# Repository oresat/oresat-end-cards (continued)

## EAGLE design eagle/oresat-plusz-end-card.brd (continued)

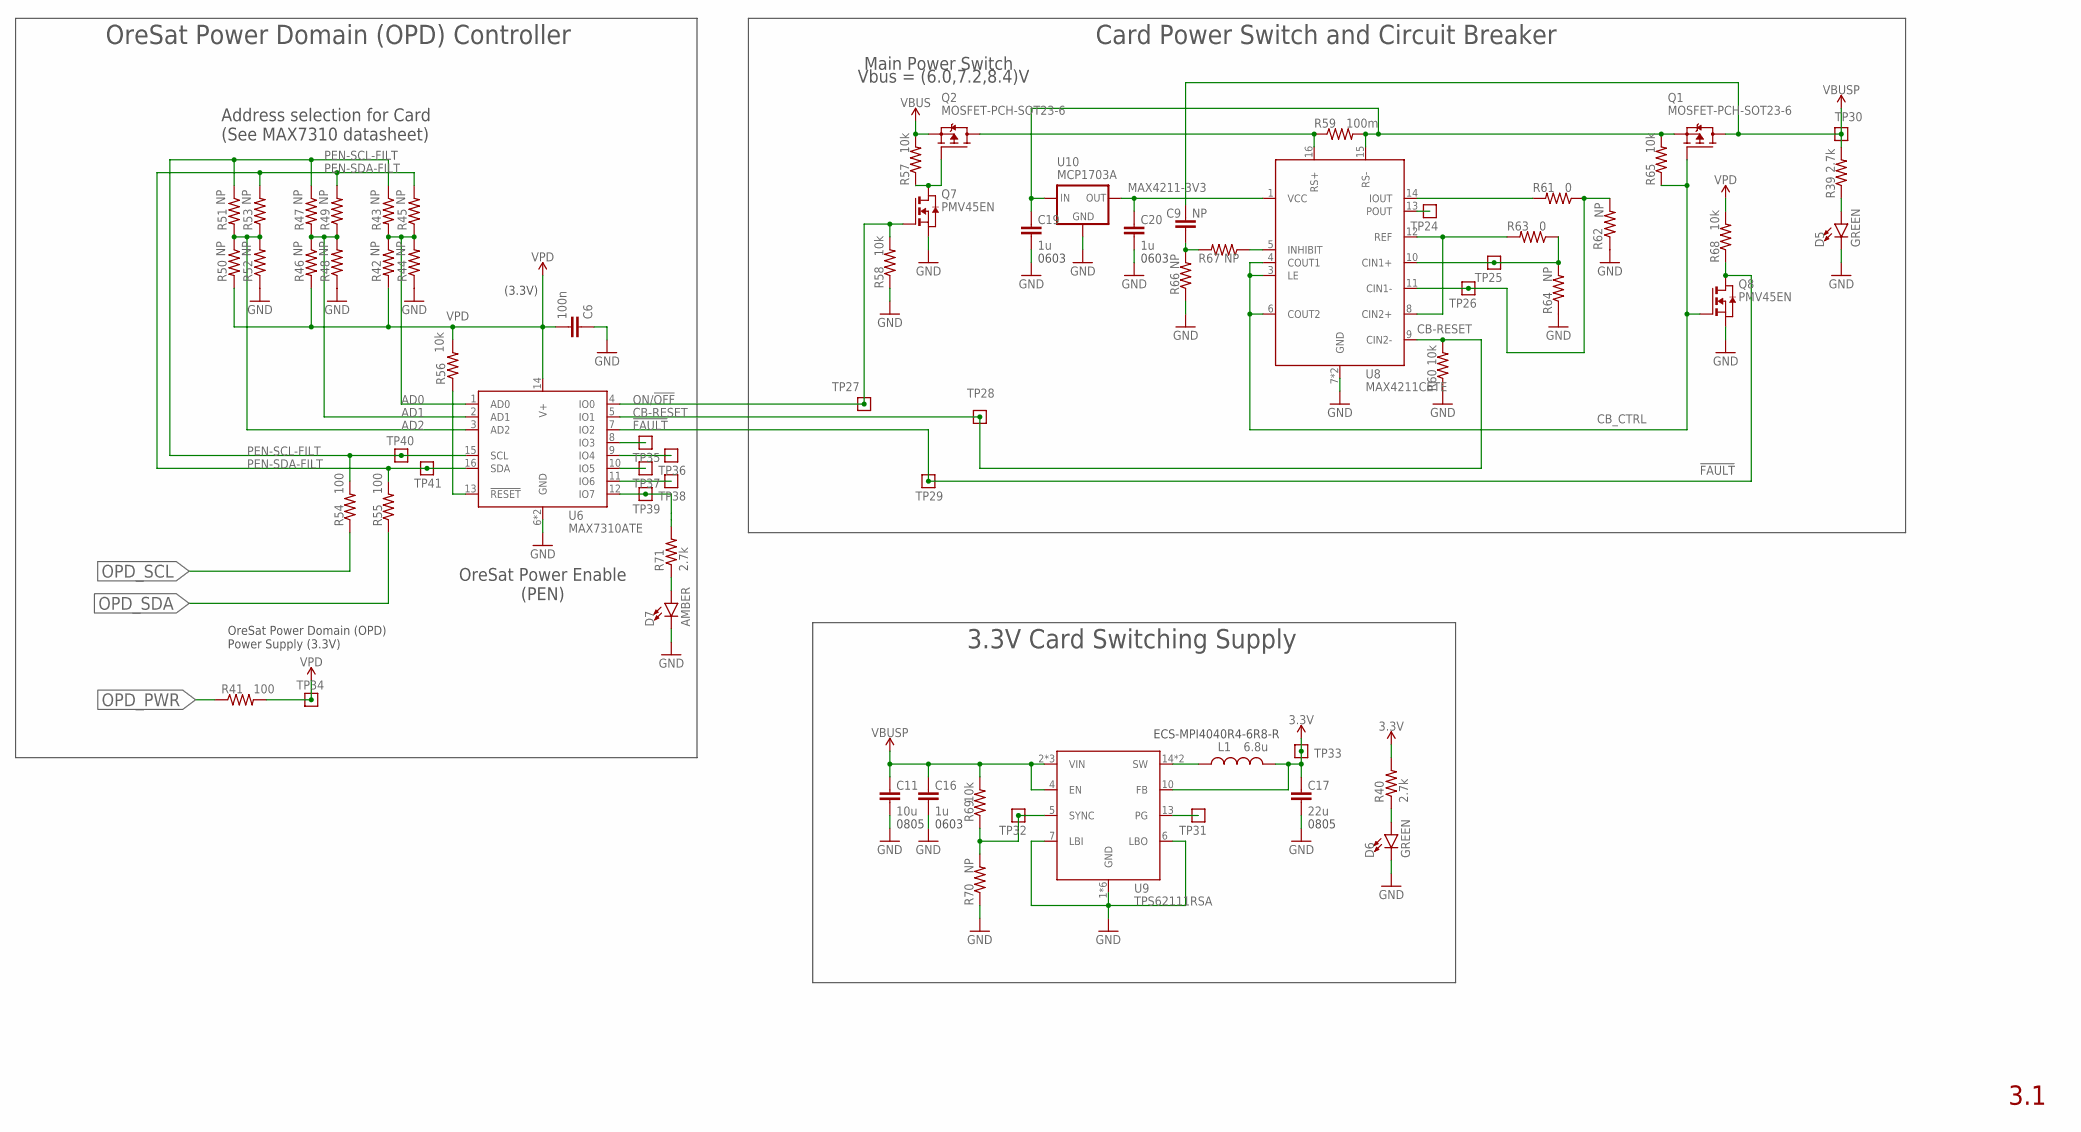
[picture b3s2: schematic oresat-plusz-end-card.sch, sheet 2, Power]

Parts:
C6: 100n; .0402-B-NOSILK; MPN CL05B104KO5NNNC
C9: NP; .0402-B-NOSILK; MPN CL05B104KO5NNNC
C11: 10u; .0805-B-NOSILK
C16, C19, C20: 1u; .0603-B-NOSILK; MPN CL05B104KO5NNNC
C17: 22u; .0805-B-NOSILK
D5, D6: GREEN; LED-0603
D7: AMBER; LED-0603
L1: 6.8u; ECS-MPI4040; MPN ECS-MPI4040R4-6R8-R
Q1, Q2: MOSFET-PCH-SOT23-6; SOT23-6; MPN DMP3050LVT-7
Q7, Q8: PMV45EN; SOT23
R39, R40, R71: 2.7k; .0402-B-NOSILK; MPN RC1005F6653CS
R41, R54, R55: 100; .0402-B-NOSILK; MPN RC1005F6653CS
R42, R43, R44, R45, R46, R47, R48, R49, R50, R51, R52, R53, R62, R64, R66, R67, R70: NP; .0402-B-NOSILK; MPN RC1005F6653CS
R56, R57, R58, R60, R65, R68, R69: 10k; .0402-B-NOSILK; MPN RC1005F6653CS
R59: 100m; R1206
R61, R63: 0; .0402-B-NOSILK; MPN RC1005F6653CS
TP24, TP25, TP26, TP27, TP28, TP29, TP30, TP31, TP32, TP33, TP34, TP35, TP36, TP37, TP38, TP39, TP40, TP41: TEST-POINT; 2MM-TEST-POINT
U6: MAX7310ATE; QFN65P400X400X80-17T210; MPN MAX7310ATE
U8: MAX4211CETE; QFN65P400X400X80-17T210; MPN MAX4211CETE
U9: TPS62111RSA; S-PVQFN-16; MPN TPS62111RSA
U10: MCP1703A; SOT23; MPN MCP1703AT-3302E/CB

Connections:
3.3V: C17.1, L1.2, R40.2, TP33.1, U9.10 (FB); also elsewhere on the board
!FAULT: Q8.3 (D), R68.1, TP29.1, U6.7 (IO2)
AD0: R42.1, R43.2, R44.2, R45.1, U6.1 (AD0)
AD1: R46.1, R47.2, R48.2, R49.1, U6.2 (AD1)
AD2: R50.1, R51.2, R52.2, R53.1, U6.3 (AD2)
CB-RESET: R60.2, TP28.1, U6.5 (IO1), U8.9 (CIN2-)
CB_CTRL: Q1.3 (G), Q8.1 (G), R65.1, U8.3 (LE), U8.4 (COUT1), U8.6 (COUT2)
GND: C6.1, C11.2, C16.2, C17.2, C19.2, C20.2, D5.C, D6.C, D7.C, Q7.2 (S), Q8.2 (S), R44.1, R48.1, R52.1, R58.1, R60.1, R62.1, R64.1, R66.1, R70.1, U6.6 (GND), U6.EPAD (GND), U8.7 (GND), U8.EPAD (GND), U9.1 (GND), U9.6 (LBO), U9.7 (LBI), U9.9 (GND), U9.11 (GND), U9.12 (GND), U9.16 (GND), U9.PAD (GND), U10.1 (GND); also elsewhere on the board
MAX4211-3V3: C20.1, U8.1 (VCC), U10.2 (OUT)
unnamed: D5.A, R39.1
unnamed: D6.A, R40.1
unnamed: R56.1, U6.13 (!RESET)
unnamed: Q2.3 (G), Q7.3 (D), R57.1
unnamed: Q2.1 (D), Q2.2 (D), Q2.5 (D), Q2.6 (D), R59.1, U8.16 (RS+)
unnamed: R61.1, R62.2, TP26.1, U8.11 (CIN1-)
unnamed: R63.1, R64.2, TP25.1, U8.10 (CIN1+)
unnamed: R61.2, U8.14 (IOUT)
unnamed: R63.2, U8.8 (CIN2+), U8.12 (REF)
unnamed: TP24.1, U8.13 (POUT)
unnamed: R67.1, U8.5 (INHIBIT)
unnamed: C9.1, R66.2, R67.2
unnamed: C19.1, Q1.4 (S), R59.2, R65.2, U8.15 (RS-), U10.3 (IN)
unnamed: TP35.1, U6.8 (IO3)
unnamed: TP36.1, U6.9 (IO4)
unnamed: TP37.1, U6.10 (IO5)
unnamed: TP38.1, U6.11 (IO6)
unnamed: R71.2, TP39.1, U6.12 (IO7)
unnamed: D7.A, R71.1
ON/!OFF: Q7.1 (G), R58.2, TP27.1, U6.4 (IO0)
OPD_PWR: R41.1; also elsewhere on the board
OPD_SCL: R54.1; also elsewhere on the board
OPD_SDA: R55.1; also elsewhere on the board
PEN-SCL-FILT: R43.1, R47.1, R51.1, R54.2, TP40.1, U6.15 (SCL)
PEN-SDA-FILT: R45.2, R49.2, R53.2, R55.2, TP41.1, U6.16 (SDA)
TPS62111-PG1: TP31.1, U9.13 (PG)
TPS62111-SYNC1: R69.1, R70.2, TP32.1, U9.5 (SYNC)
TPS62111_SW1: L1.1, U9.14 (SW), U9.15 (SW)
VBUS: Q2.4 (S), R57.2; also elsewhere on the board
VBUSP: C9.2, C11.1, C16.1, Q1.1 (D), Q1.2 (D), Q1.5 (D), Q1.6 (D), R39.2, R69.2, TP30.1, U9.2 (VIN), U9.3 (VIN), U9.4 (EN), U9.8 (VIN)
VPD: C6.2, R41.2, R42.2, R46.2, R50.2, R56.2, R68.2, TP34.1, U6.14 (V+)

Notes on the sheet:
Main Power Switch
OreSat Power Enable (PEN)
Address selection for Card (See MAX7310 datasheet)
(3.3V)
0805
0603
ECS-MPI4040R4-6R8-R
Vbus = (6.0,7.2,8.4)V
OreSat Power Domain (OPD) Power Supply (3.3V)
OreSat Power Domain (OPD) Controller
3.3V Card Switching Supply
Card Power Switch and Circuit Breaker
3.1

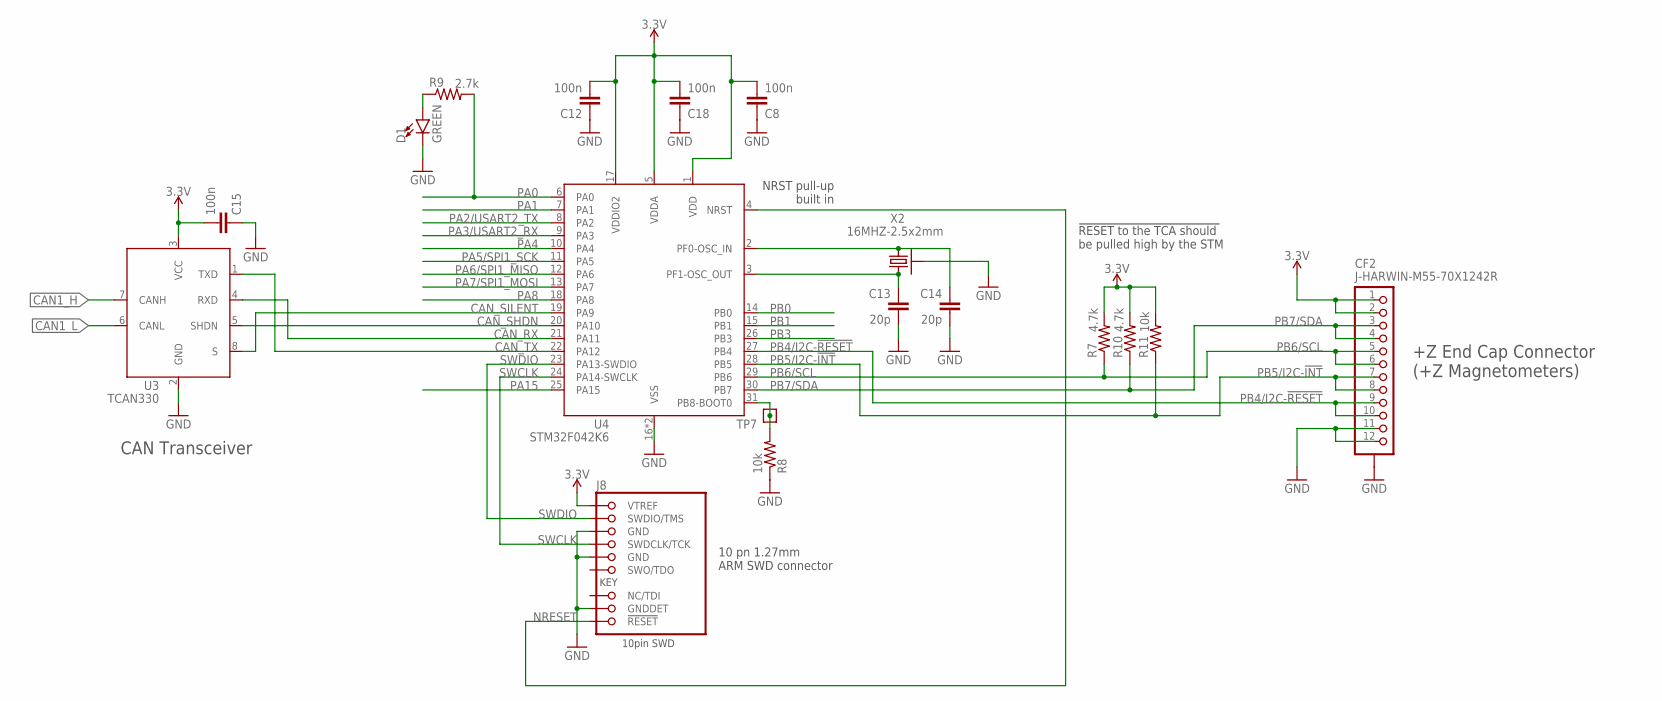
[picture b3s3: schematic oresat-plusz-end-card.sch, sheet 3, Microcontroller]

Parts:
C8, C12, C15, C18: 100n; .0402-B-NOSILK; MPN CL05B104KO5NNNC
C13, C14: 20p; .0402-B-NOSILK; MPN CL05C200JB51PNC
CF2: J-HARWIN-M55-70X1242R; HARWIN-M55-70X1242R
D1: GREEN; LED-0603
J8: FTSH-105-XX-X-DV-K; CON10_2X5_DUK_FTSH; MPN 3220-10-0100-00
R7, R10: 4.7k; .0402-B-NOSILK; MPN RC1005F6653CS
R8, R11: 10k; .0402-B-NOSILK; MPN RC1005F6653CS
R9: 2.7k; .0402-B-NOSILK; MPN RC1005F6653CS
TP7: TEST-POINT; 2MM-TEST-POINT
U3: TCAN330; SOT23-8_TI-DCN; MPN TCAN330GDCNT
U4: STM32F042K6; QFP32-7X7; MPN STM32F042K6T7
X2: 16MHZ-2.5x2mm; CRYSTAL_2.5X2; MPN ECS-160-10-36Q-ES-TR

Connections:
3.3V: C8.2, C12.2, C15.2, C18.2, CF2.1, CF2.2, J8.1 (VTREF), R7.2, R10.2, R11.2, U3.3 (VCC), U4.1 (VDD), U4.5 (VDDA), U4.17 (VDDIO2); also elsewhere on the board
BOOT1: R8.2, TP7.1, U4.31 (PB8-BOOT0)
CAN1_H: U3.7 (CANH); also elsewhere on the board
CAN1_L: U3.6 (CANL); also elsewhere on the board
CAN_RX: U3.4 (RXD), U4.21 (PA11)
CAN_SHDN: U3.5 (SHDN), U4.20 (PA10)
CAN_SILENT: U3.8 (S), U4.19 (PA9)
CAN_TX: U3.1 (TXD), U4.22 (PA12)
CRYSTALIN1: C14.1, U4.2 (PF0-OSC_IN), X2.1
CRYSTALOUT1: C13.1, U4.3 (PF1-OSC_OUT), X2.3 (2)
GND: C8.1, C12.1, C13.2, C14.2, C15.1, C18.1, CF2.11, CF2.12, CF2.P$1 (SHIELDS), CF2.P$2 (SHIELDS), CF2.P$3 (SHIELDS), CF2.P$4 (SHIELDS), D1.C, J8.3 (GND), J8.5 (GND), J8.9 (GNDDET), R8.1, U3.2 (GND), U4.16 (VSS), U4.32 (VSS), X2.2 (SHIELD), X2.4 (SHIELD); also elsewhere on the board
unnamed: D1.A, R9.1
NRESET: J8.10 (!RESET), U4.4 (NRST)
PA0: R9.2, U4.6 (PA0)
PA1: U4.7 (PA1)
PA2/USART2_TX: U4.8 (PA2)
PA3/USART2_RX: U4.9 (PA3)
PA4: U4.10 (PA4)
PA5/SPI1_SCK: U4.11 (PA5)
PA6/SPI1_MISO: U4.12 (PA6)
PA7/SPI1_MOSI: U4.13 (PA7)
PA8: U4.18 (PA8)
PA15: U4.25 (PA15)
PB0: U4.14 (PB0)
PB1: U4.15 (PB1)
PB3: U4.26 (PB3)
PB4/I2C-!RESET: CF2.9, CF2.10, U4.27 (PB4)
PB5/I2C-!INT: CF2.7, CF2.8, R11.1, U4.28 (PB5)
PB6/SCL: CF2.5, CF2.6, R7.1, U4.29 (PB6)
PB7/SDA: CF2.3, CF2.4, R10.1, U4.30 (PB7)
SWCLK: J8.4 (SWDCLK/TCK), U4.24 (PA14-SWCLK)
SWDIO: J8.2 (SWDIO/TMS), U4.23 (PA13-SWDIO)

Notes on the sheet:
+Z End Cap Connector (+Z Magnetometers)
NRST pull-up built in
10 pn 1.27mm ARM SWD connector
CAN Transceiver
!RESET to the TCA should be pulled high by the STM

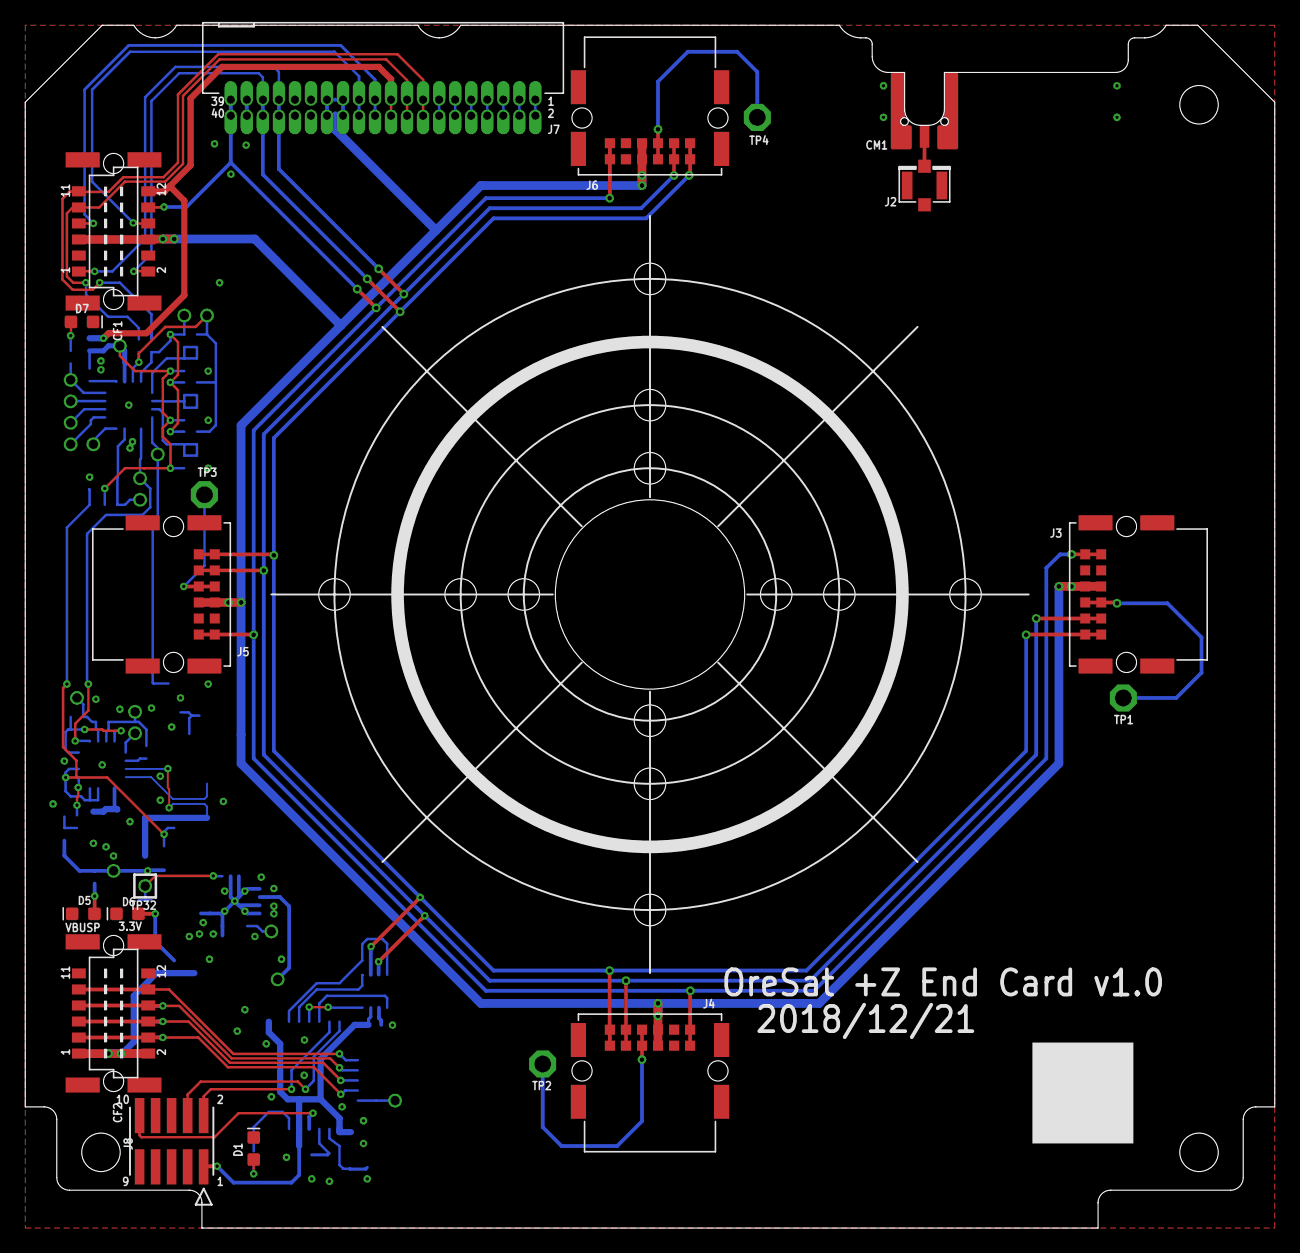
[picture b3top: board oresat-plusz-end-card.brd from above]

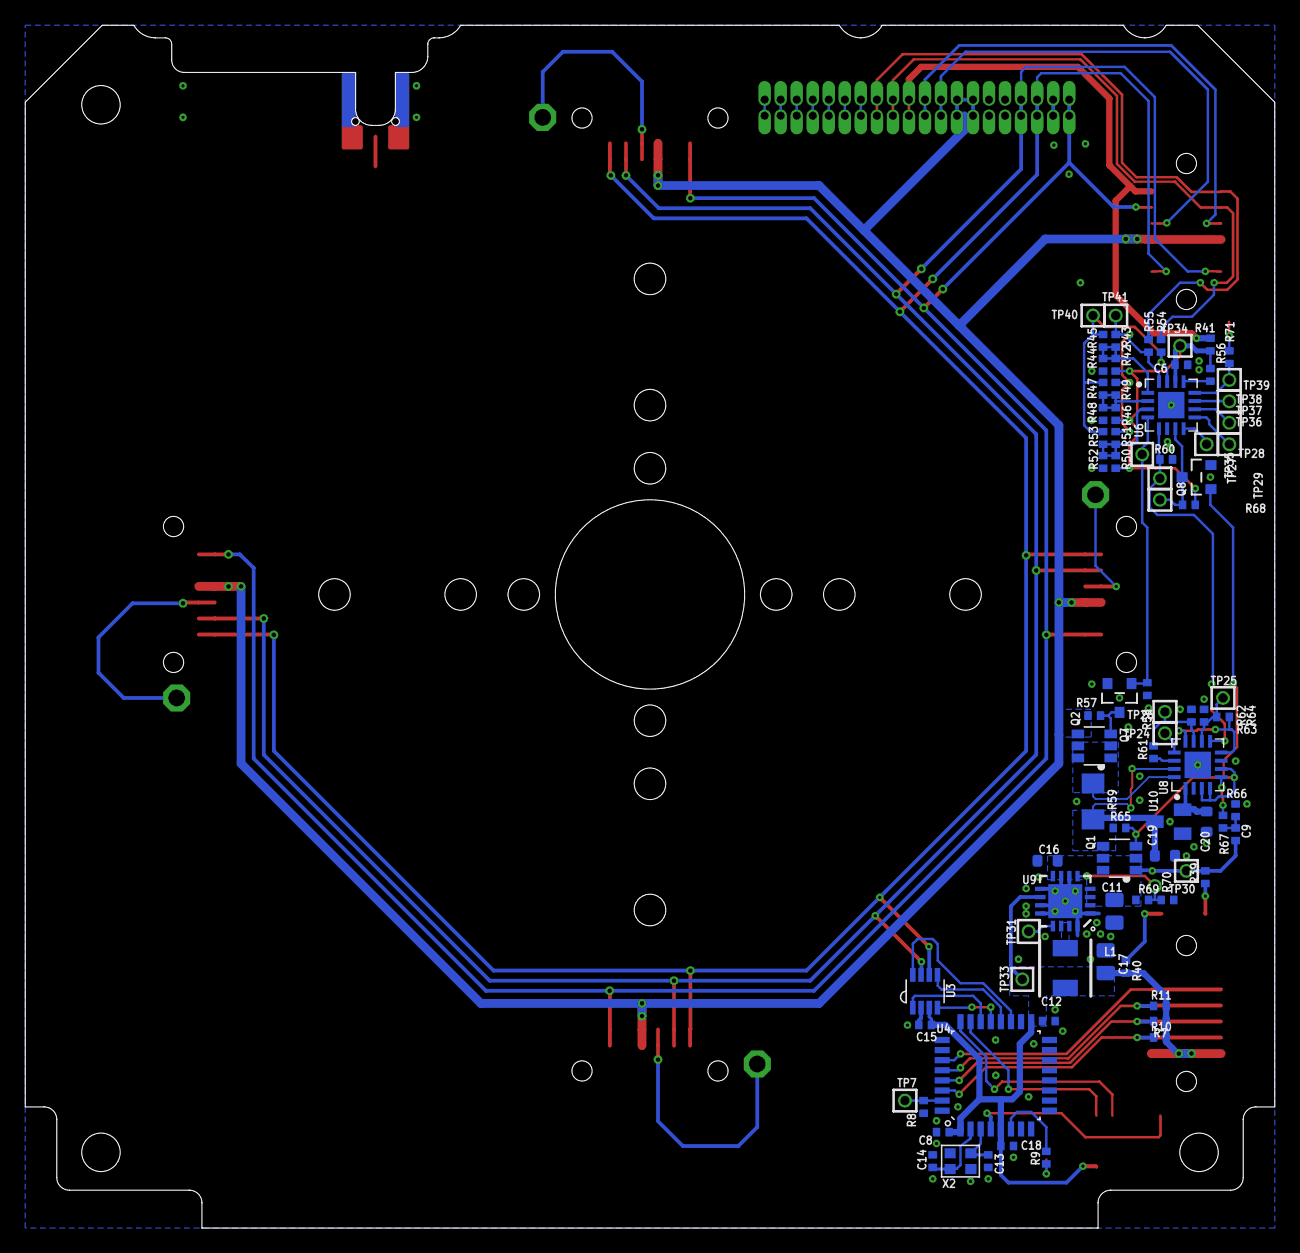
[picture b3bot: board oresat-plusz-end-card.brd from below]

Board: 2 copper layers, 99.0 x 95.3 mm, 104 parts (81 on the bottom side), 73 nets.

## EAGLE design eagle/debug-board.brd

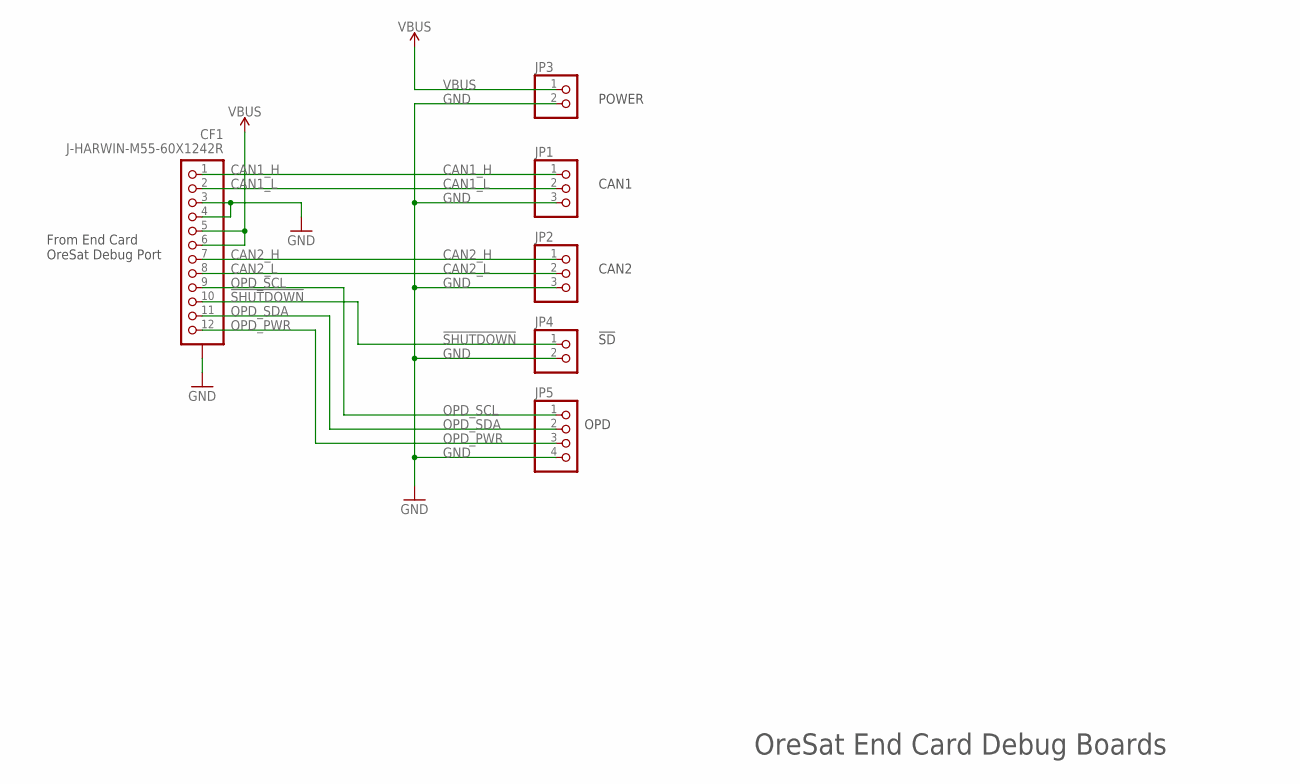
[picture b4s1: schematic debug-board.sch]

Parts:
CF1: J-HARWIN-M55-60X1242R; HARWIN-M55-60X1242R
JP1, JP2: PINHD-1X3; 1X03
JP3, JP4: PINHD-1X2; 1X02
JP5: PINHD-1X4; 1X04

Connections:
!SHUTDOWN: CF1.10, JP4.1
CAN1_H: CF1.1, JP1.1
CAN1_L: CF1.2, JP1.2
CAN2_H: CF1.7, JP2.1
CAN2_L: CF1.8, JP2.2
GND: CF1.3, CF1.4, CF1.P$1 (SHIELDS), CF1.P$2 (SHIELDS), CF1.P$3 (SHIELDS), CF1.P$4 (SHIELDS), JP1.3, JP2.3, JP3.2, JP4.2, JP5.4
OPD_PWR: CF1.12, JP5.3
OPD_SCL: CF1.9, JP5.1
OPD_SDA: CF1.11, JP5.2
VBUS: CF1.5, CF1.6, JP3.1

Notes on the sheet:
POWER
CAN1
CAN2
!SD
OPD
OreSat End Card Debug Boards
From End Card OreSat Debug Port

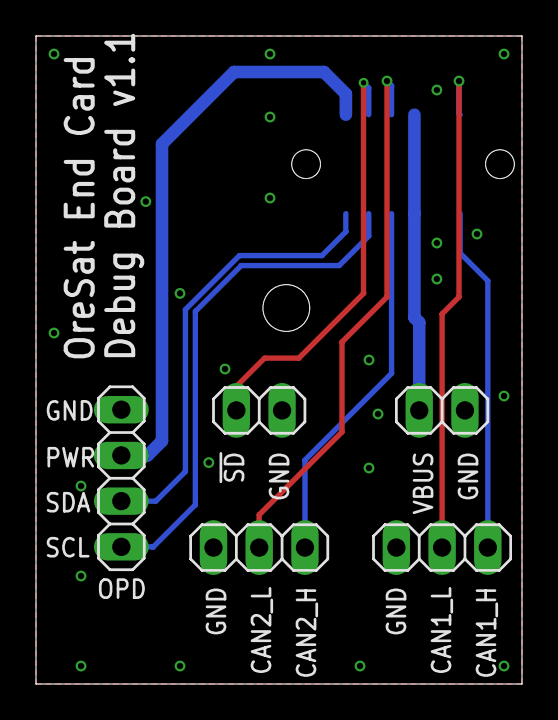
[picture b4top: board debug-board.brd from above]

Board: 2 copper layers, 27.0 x 36.0 mm, 6 parts (1 on the bottom side), 10 nets.

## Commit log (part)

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2018-12-16 Outline of boards, license file, readme.
2018-12-17 Created library and placed solar connectors based on structure updates from yesterday.
2018-12-19 Worked with Joe to check connectors, preliminary layout, 2 layers for now.
2018-12-21 Updated +Z end card, with end cap attachment to magnetometers.
2018-12-22 +Z end cards ready for mfg, as far as we know!
2019-02-26 Added debug board that comes off of the +Z and -Z end cards (past the caps).
2019-02-26 Updated end cards with antenna keep outs, and rewired +Z end card debug port and started on +Z schematic update with power domain.
2019-02-27 Added OreSat power domain -- via design blocksgit status -- and OMG it's doneish.
2020-11-23 Moved OreSat0 +Z end card and mezzanine to the end card directory, where it really ought to have been. Updated the card and mezanine with Card outline v1.3, and added a first pass of the S band feed 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
2020-11-24 Final cleanup and polish of v1.1 OreSat0 +Z end card and mezzanine. Fixed S band 1/4 wave, lots of stiching and polish, fixed radial TCREAM on the contact pads, lots of TNAMES polish.
2020-11-24 Clean up BOM and part numbers. Ready for v1.1 fab.
2020-11-24 Switched to a QCN-27D+ (with DC passthrough) for S band, and made the U and L band 1/4 wave lengths a bit more precise after getting precise lengths from Eric.
2020-12-08 Small tweaks; reduced mezanine board size. Added flight tags. Off to fab!
2021-01-04 Forgot to remove a meltwire resistor.
2021-04-08 Version 1.2 of the OreSat0 end card and mezzanine.
    Largest change is the position of the antennas on the end card; changes to the deployer changed the antenna placement which triggered everything else.
    Other changes include fiducials, attributes cleanup, move to 0603 resistors, and misc polish.
2021-04-21 Fixed bad part number for end card to end cap connector.
2021-10-03 replaced S-band net labels with L1-band labels, swapped the S-band hybrids with L-band hybrids, recalculated 1/4 wavelength trace length, routed a new short+1/4 wavelength trace
2021-10-10 added vias along new short+1/4wave trace
2021-10-10 added bstop new short+1/4wave trace
2021-10-10 adjusted the length of L1BAND_0 and L1BAND_90 to match L1BAND_180 and L1BAND_270
2021-10-10 adjusted bstop for L1BAND_0 AND L1BAND_90
2021-11-04 v2.0 card, mezzanine, and BOM for v2.0. Moved UHF hybrids to avoid melt wire resistor leads. Updated BOM to reflect new v2.0 design.
2021-11-04 Added in-stock quantities
2022-07-27 Moved -z to KiCad and labeled RF connectors
2022-07-27 Move OreSat0 +Z end card to its own directory; removed amazingly old end cards that aren't relevant anymore.
2022-07-27 Fixed some errors on the ancient -z end card
2022-07-27 Removed the ancient -z end card
2022-07-27 renamed OreSat0 +Z end card to a more descriptive, non-mission name
2022-07-27 Updated liscense to V2
2022-07-27 Moved +z with turnstile to KiCad
2022-07-27 Added generic +z end card
2023-02-12 Renamed folders to satellite names as per other repos
2023-02-19 Added generic minusZ end card
2023-02-19 Added generic variant of the OreSat0.5 -Z end card
2023-02-19 Added new outline
2023-02-19 Added new outine
2023-02-19 First rev of OreSat0.5 +Z end card. Updated helical deployer, removed as much EAGLE cruft as easily possible, killed multiple sch sheets.
2023-02-20 More KiCADing, new fiducials and footprints, fixed ERC and DRC. Now waiting on Cesar to do stuff.
2023-02-20 Updated filename for OreSat0.5 +Z end card
2023-02-20 Updated +Z end card connector symbols
2023-02-20 Fixed +Z end card backplane connector library warning
2023-02-20 Updated -Z end card and replaced eagle imported libraries with kicad libraries
2023-02-20 -Z end card design review changes, and added antenna feeds
2023-02-21 Added helical landing pad and left hopefully enough room for Garrett to put in matching components.
2023-02-21 Rounded out RF trace corners on -Z end card
2023-02-21 added Matching Components
    Added matching components for s band antenna, ground stitching
2023-02-21 Updated CAM settings on PCB.
2023-02-21 OMG what happened to the names of this card? Fixing.
2023-02-21 fix silkscreen for -z end card
2023-02-21 Updated readme, moved generic to not oresat0.5
2023-02-21 removing build files, how did these even get added?
2023-02-21 CAM file changes for end card PCBs.
2023-07-17 Updated OreSat 0.5 end card board outlines and mounting holes, and fixed KiCad library warnings
2023-07-28 Updated -Z end card and DXF
2023-07-28 Updated -Z end card date/version number on silkscreen
2023-09-03 Updated -Z end card
2023-09-03 Updated +Z end card
2023-09-11 Updated mounting hole on +Z end card
2023-09-15 Fixed up OreSat0.5 -Z end card: Added hole for U.FL connector to get to GPS antnena, fixed library paths which seemed broken, replaced older EAGLE files too, fixed schematic/board disconnect with ref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
2023-09-15 Oresat0.5 +Z end card: v1.1. Updated to latest KiCAD.
2023-09-15 Fixed mispelling in name
2023-12-15 Moves antenna connection from large vias to slots so we don't need an a lead on the 1/4 inch tape measure antennas.
2024-02-26 Added latest DXF of card outline.
2024-02-26 Updated +Z end card mounting holes
2024-02-26 Added RF strip across hole to keep out ground plane.
2024-03-22 Updated solar module connector positions
2024-03-24 Added updated detailed DXF for +Z end card
2024-04-01 Updated date and unecessary polish on planes, including fillets and just more planes with more vias.
2024-04-01 Updated date, and unecessary and obsessive widening and smoothing of planes.
2024-04-28 Updated helical matching network components and values
2024-05-06 Added M2 fastener holes back into the -Z end card. Rev'd to v1.4.
2024-08-19 initial mounting holes changes for new deployer
2024-08-20 Revert "initial mounting holes changes for new deployer" -- oops, wrong end card.
    This reverts commit 281d3ddd2ce643add95357c75bebd497bf0c76a9.
2024-08-20 Updated hole positions for single door deployer. TODO: fix weird net class errors that shouldn't exist.
2024-09-10 changed resistor placement
2024-09-11 fixed silkscreen, fixed resistor helical deployer zone
2024-09-19 added components in symbol field for BOM
2024-09-20 Final polish for v1.4. Added more stiching vias, cleaned up some DRCs that were stupid, added more layers to deployment resistor pads, now sending off to Osh Park.
2024-11-03 R2 and J6 excluded from BOM and set as DNP
2025-09-23 Moved Mezz Eagle Files to Their Own Folder
2025-09-23 Imported Mezz Files to KiCAD
2025-09-23 Fixed Spelling Mistake
2025-09-23 Fixed Board Outline
2026-01-11 Creating OreSat1 end card folder for Spencer to start adding OPD deployer circuitry. Also probably needs updates for +Z end card for new helical deployer.
2026-02-01 add OPD and deployer circuitry
2026-02-01 add OPD and deployer circuitry, some fixes needed
2026-02-10 v1.1
2026-02-17 v1.2
2026-02-18 v1.1, theoretically done
2026-02-19 v1.3, theoretically done
2026-02-24 OreSat1 -Z end card update
    Upgraded symbols, fixed BOM and added presets, and added UART switches for new solar modules. Clleaned up layout, including some planes and footprints. Still more left to do, but it's more ready to g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
2026-02-26 Rerouted -Z endcard & created new file for ESI dipole v1
2026-02-26 moved esi file out of oresat
2026-02-27 Changed symbols & fab layout
2026-02-27 Design review, more to do!
2026-03-01 Dipole schematic: added balun & footprints. Pre-tracing
2026-03-02 Started RF tracing, not complete -- maybe need to move the balun b/c microstrip turns are too sharp
2026-03-05 renamed ESI -Z end card to combat Shae's weird naming conventions
2026-03-06 Finalized dipole changes, added -/+ Y solar mods. Believe this is finished
2026-03-08 shifted and softened microstrip curves
2026-03-09 bom finished
2026-03-09 Fixed schematic label issues and routed solar uarts
2026-03-09 fixed shcematic issues and routing, updated footprints
2026-03-09 mounting hole parity fix (internal screaming)
2026-03-10 is it fixed?
2026-03-10 Fixed weird footprint sync error that kept popping up on DRC around the mounting holes because of the polygon zone keepout areas. Also found a huge mistake in the schematic, fixed, still needs to be 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
2026-03-10 Whoops, fixed silly ERC errors
2026-03-11 Fixed HW errors
2026-03-11 Fixed OPD connection in schematics and updated tracing and out of date footprints. Ready for final review from andrew
2026-03-11 FIxed OPD connection
2026-03-11 added clearance around HW
2026-03-12 SBAND & HELICAL RF CHANGES
2026-03-12 Another round on the +Z End Card; ready for fab.
    Brushed up RF paths and solder mask, cleaned up UART switches with closer bypass caps, cleaned up a lot of the zones, and lots of little polishing.
2026-03-15 Align SMPM connectors better and add a bit more solder mask keepout
2026-03-24 v1.1 sent to fab
    Updated 3D models of connectors, added missing capacitors, fixed footprints, polished schematic, upgraded to single README file with Makefile.
2026-04-13 ESI v1.0 -Z End Card for fab
    Added makefile and readme, fixed BOM error, moved to better RF zone rules
2026-06-07 Update gitignore for KiCad 10
2026-06-07 ESI -Z End Card updated to v1.1 with extremely minor changes (KiCad 10 update)
    Updated to KiCad 10.0.3, which updated several footprints and re-triggered from ERC
    and DRCs. Those were fixed, and out of an abundance of caution, we upped the version
    number although there's no significant difference with v1.0.
2026-06-07 Importing OreSat0 +Z End Card + Turnstile EAGLE files into a generic +Z end card file for KiCad
    We flew OreSat0 in 2022 with a tri-band turnstile. All files were EAGLE PCB files. This just imports the EAGLE files
    as KiCad files, but they're going ot require a LOT of work to upgrade them to OreSat1 tech.
2026-06-26 Swapped L and L1 Bands
